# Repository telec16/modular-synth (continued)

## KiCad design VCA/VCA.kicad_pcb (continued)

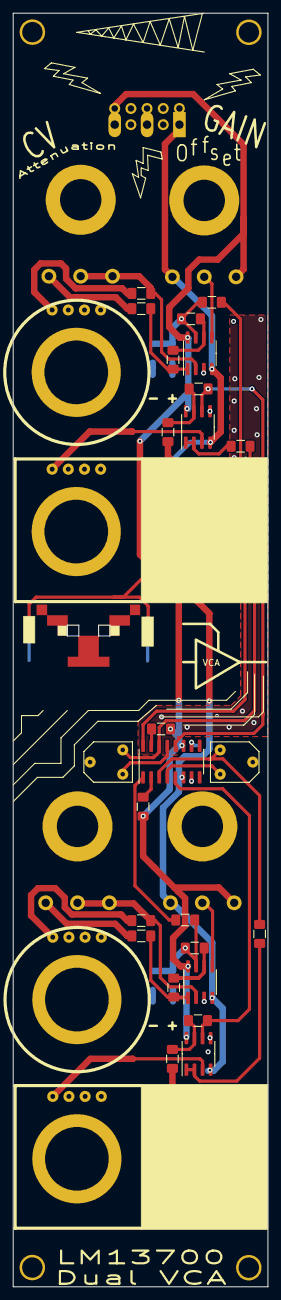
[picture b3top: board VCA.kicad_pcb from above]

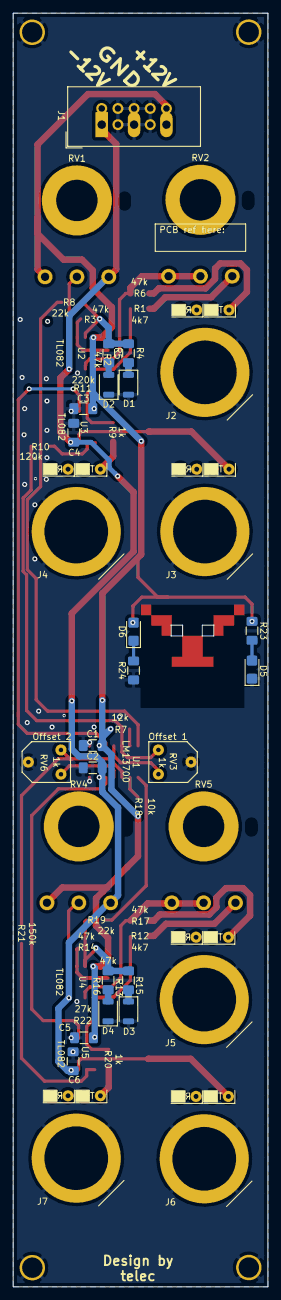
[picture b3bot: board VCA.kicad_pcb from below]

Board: 2 copper layers, 40.0 x 200.0 mm, 57 parts (19 on the bottom side), 41 nets.

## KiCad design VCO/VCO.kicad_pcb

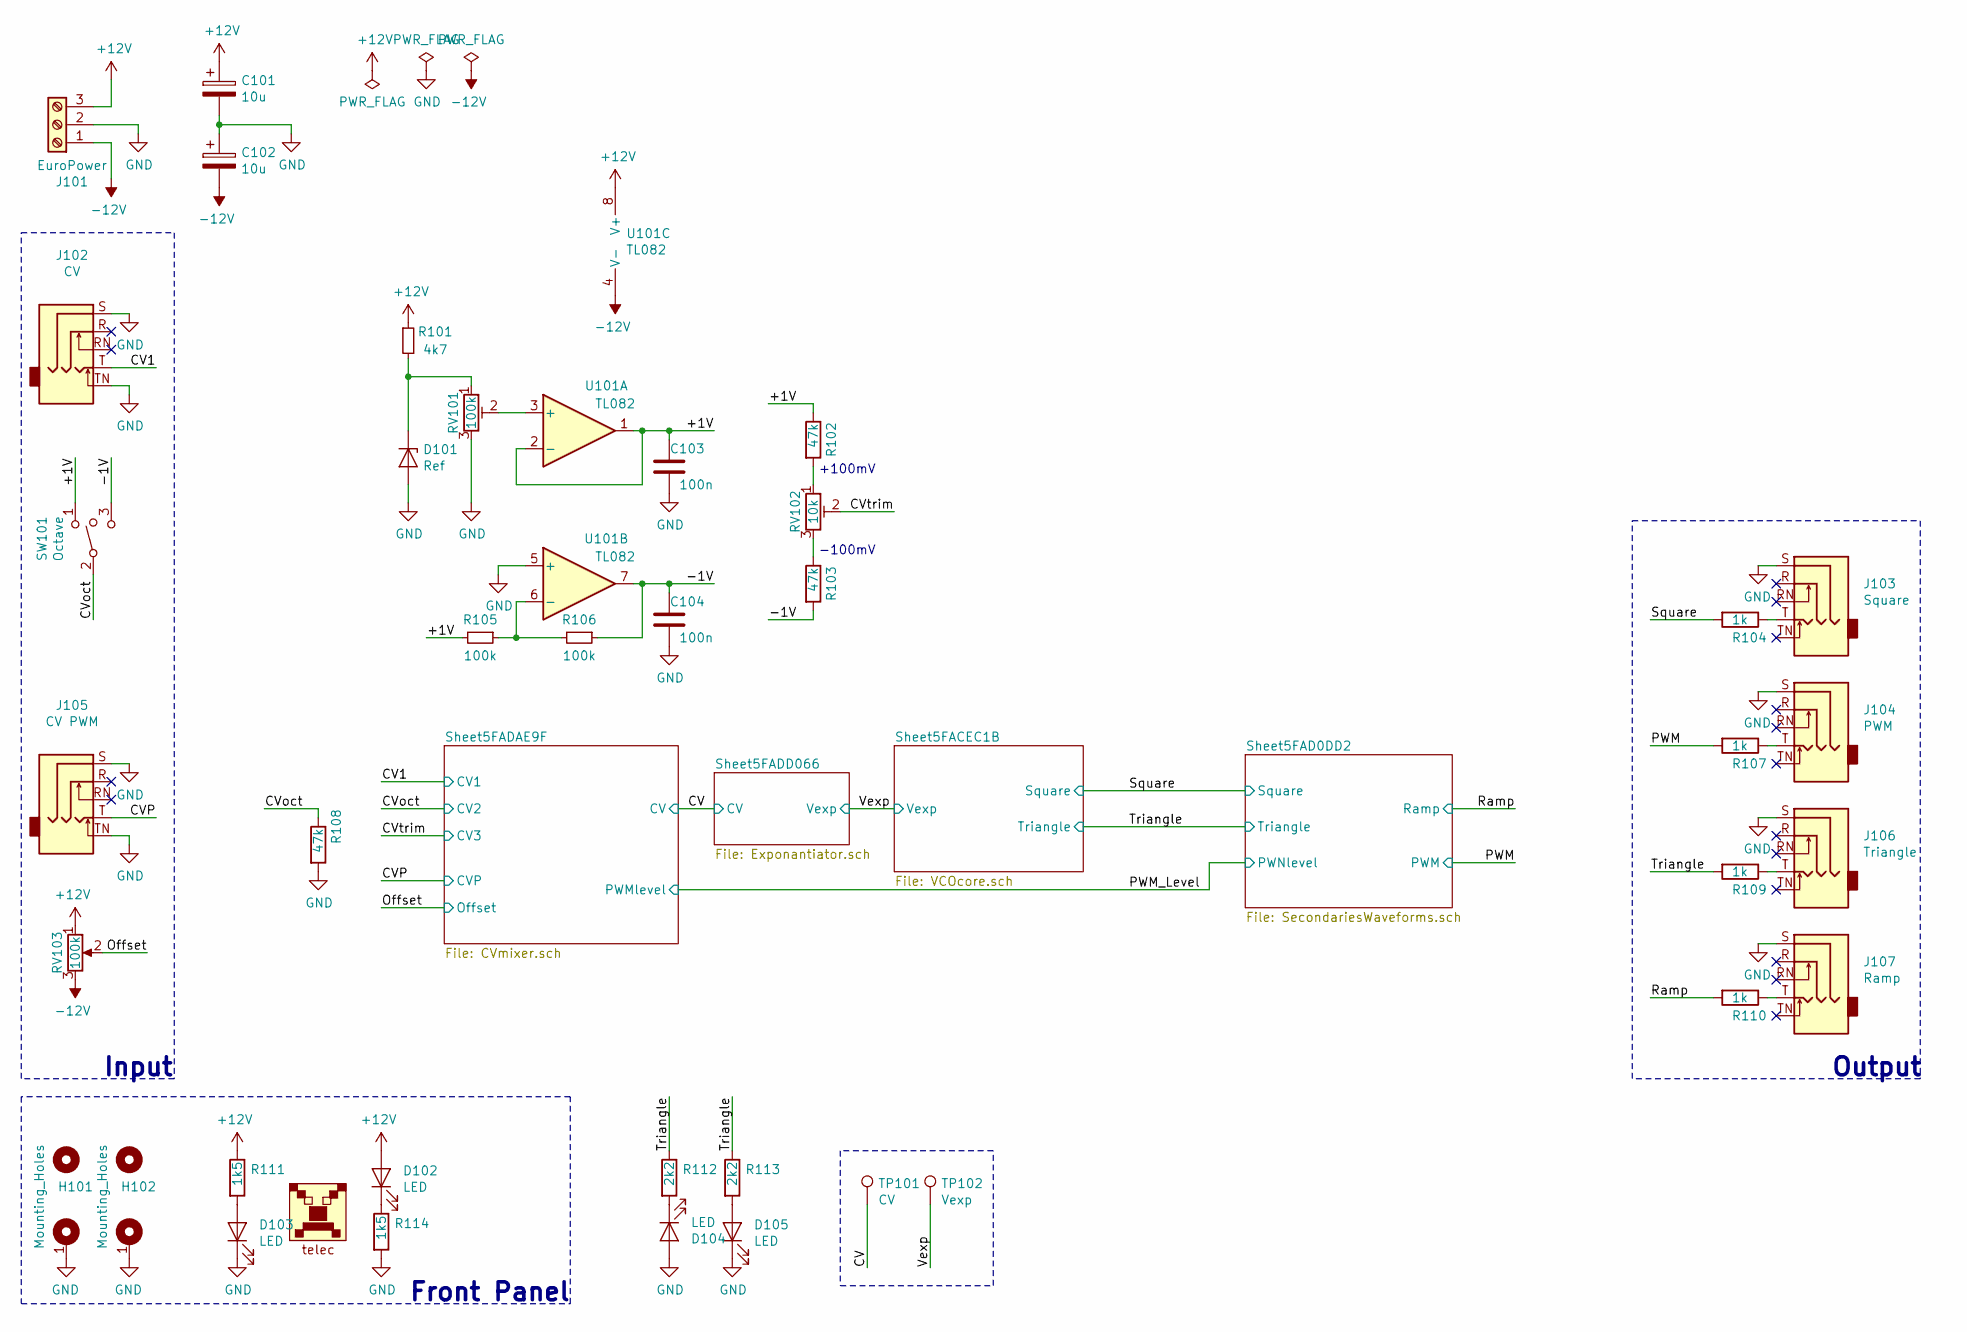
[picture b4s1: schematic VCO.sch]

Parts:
C101, C102: 10u; CP_Radial_D6.3mm_P2.50mm
C103, C104: 100n; C_0805_2012Metric_Pad1.15x1.40mm_HandSolder
D101: Ref; D_1206_3216Metric_Pad1.42x1.75mm_HandSolder
D102, D103: LED; LED_1206_3216Metric_Castellated
D104, D105: LED; LED_1206_3216Metric_ReverseMount_Hole1.8x2.4mm
H101, H102: Mounting_Holes; Kosmo_Panel_Dual_Mounting_Holes
J101: EuroPower
J102: CV; Jack_Hole_Square
J103: Square; Jack_Hole_Square
J104: PWM; Jack_Hole_Square
J105: CV PWM; Jack_Hole_Square
J106: Triangle; Jack_Hole_Square
J107: Ramp; Jack_Hole_Square
LOGO101: telec; telec-16
R101: 4k7; R_1206_3216Metric_Pad1.42x1.75mm_HandSolder
R102, R103, R108: 47k; R_Axial_DIN0204_L3.6mm_D1.6mm_P7.62mm_Horizontal
R104, R107, R109, R110: 1k; R_1206_3216Metric_Pad1.42x1.75mm_HandSolder
R105, R106: 100k; R_1206_3216Metric_Pad1.42x1.75mm_HandSolder
R111, R114: 1k5; R_1206_3216Metric_Pad1.42x1.75mm_HandSolder
R112, R113: 2k2; R_1206_3216Metric_Pad1.42x1.75mm_HandSolder
RV101: 100k; Potentiometer_Bourns_3296W_Vertical
RV102: 10k; Potentiometer_Bourns_3296W_Vertical
RV103: 100k; Potentiometer_Single_Vertical_Hole
SW101: Octave; Switch_Hole
TP101: CV; PinHeader_1x01_P2.54mm_Vertical
TP102: Vexp; PinHeader_1x01_P2.54mm_Vertical
U101: TL082; SOIC-8_3.9x4.9mm_P1.27mm

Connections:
+12V: C101.1, D102.2 (A), J101.3, R101.1, R111.1, RV103.1, U101.8 (V+); also elsewhere on the board
-12V: C102.2, J101.1, RV103.3, U101.4 (V-); also elsewhere on the board
/+1V: C103.1, R102.1, R105.2, SW101.1, U101.1, U101.2 (-)
/-1V: C104.1, R103.2, R106.1, SW101.3, U101.7
/CV: TP101.1; also elsewhere on the board
/CV1: J102.T; also elsewhere on the board
/CVP: J105.T; also elsewhere on the board
/CVoct: R108.1, SW101.2; also elsewhere on the board
/CVtrim: RV102.2; also elsewhere on the board
/Offset: RV103.2; also elsewhere on the board
/PWM: R107.2; also elsewhere on the board
/Ramp: R110.2; also elsewhere on the board
/Square: R104.2; also elsewhere on the board
/Triangle: R109.2, R112.1, R113.1; also elsewhere on the board
/Vexp: TP102.1; also elsewhere on the board
GND: C101.2, C102.1, C103.2, C104.2, D101.2 (A), D103.1 (K), D104.2 (A), D105.1 (K), H101.1, H102.1, J101.2, J102.S, J102.TN, J103.S, J104.S, J105.S, J105.TN, J106.S, J107.S, R108.2, R114.2, RV101.3, U101.5 (+); also elsewhere on the board
unnamed: D101.1 (K), R101.2, RV101.1
unnamed: D102.1 (K), R114.1
unnamed: D103.2 (A), R111.2
unnamed: D104.1 (K), R112.2
unnamed: D105.2 (A), R113.2
unnamed: J103.T, R104.1
unnamed: J104.T, R107.1
unnamed: J106.T, R109.1
unnamed: J107.T, R110.1
unnamed: R102.2, RV102.1
unnamed: R103.1, RV102.3
unnamed: R105.1, R106.2, U101.6 (-)
unnamed: RV101.2, U101.3 (+)

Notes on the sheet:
Output
Input
Front Panel
+100mV
-100mV

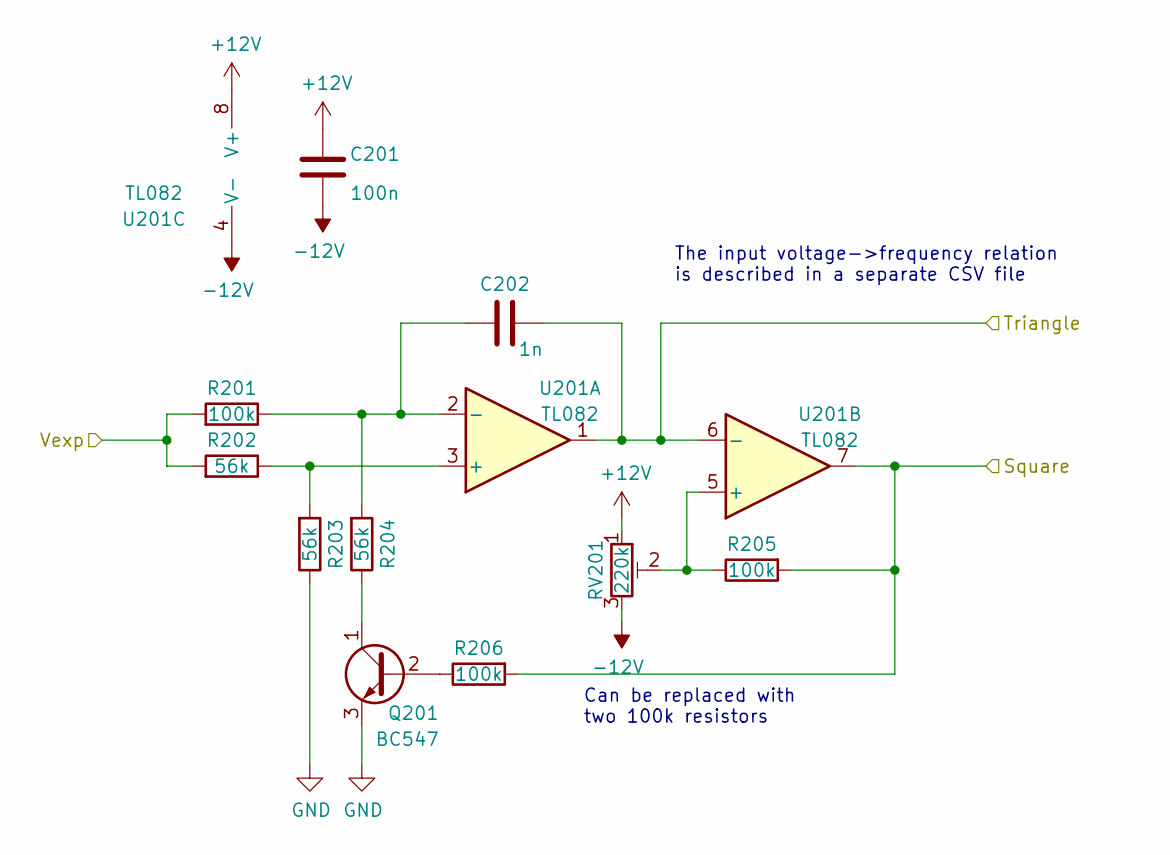
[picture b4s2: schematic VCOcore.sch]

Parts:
C201: 100n; C_0805_2012Metric_Pad1.15x1.40mm_HandSolder
C202: 1n; C_Disc_D7.0mm_W2.5mm_P5.00mm
Q201: BC547; TO-92_Inline_Wide
R201, R205, R206: 100k; R_Axial_DIN0204_L3.6mm_D1.6mm_P7.62mm_Horizontal
R202, R203, R204: 56k; R_Axial_DIN0204_L3.6mm_D1.6mm_P7.62mm_Horizontal
RV201: 220k; Potentiometer_P3.81mmx5.12mm_Vertical
U201: TL082; DIP-8_W7.62mm_LongPads

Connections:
+12V: C201.1, RV201.1, U201.8 (V+); also elsewhere on the board
-12V: C201.2, RV201.3, U201.4 (V-); also elsewhere on the board
/Square: R205.2, R206.2, U201.7; also elsewhere on the board
/Triangle: C202.1, U201.1, U201.6 (-); also elsewhere on the board
/Vexp: R201.2, R202.2; also elsewhere on the board
GND: Q201.3 (E), R203.1; also elsewhere on the board
unnamed: C202.2, R201.1, R204.2, U201.2 (-)
unnamed: Q201.1 (C), R204.1
unnamed: Q201.2 (B), R206.1
unnamed: R202.1, R203.2, U201.3 (+)
unnamed: R205.1, RV201.2, U201.5 (+)

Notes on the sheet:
Can be replaced with two 100k resistors
The input voltage->frequency relation is described in a separate CSV file

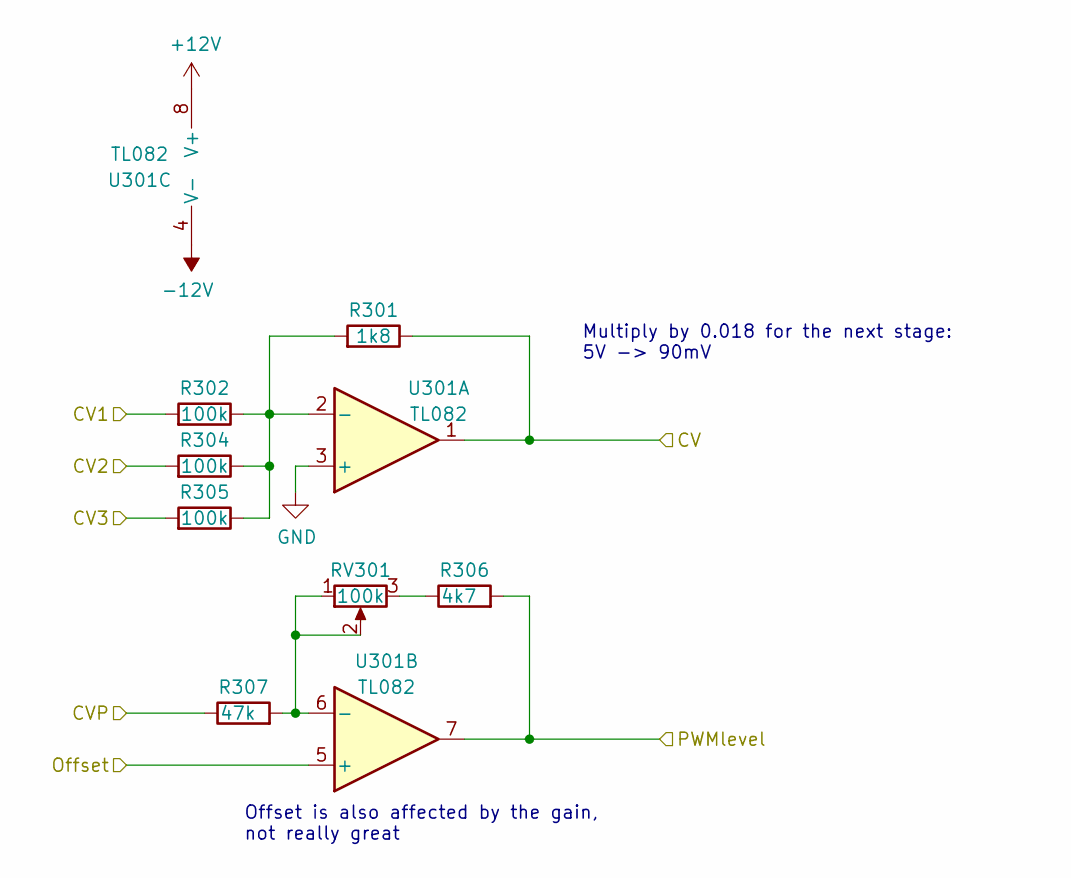
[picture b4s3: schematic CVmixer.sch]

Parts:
R301: 1k8; R_Axial_DIN0204_L3.6mm_D1.6mm_P7.62mm_Horizontal
R302, R304, R305: 100k; R_Axial_DIN0204_L3.6mm_D1.6mm_P7.62mm_Horizontal
R306: 4k7; R_Axial_DIN0204_L3.6mm_D1.6mm_P7.62mm_Horizontal
R307: 47k; R_Axial_DIN0204_L3.6mm_D1.6mm_P7.62mm_Horizontal
RV301: 100k; Potentiometer_Single_Vertical_Hole
U301: TL082; DIP-8_W7.62mm_LongPads

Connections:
+12V: U301.8 (V+); also elsewhere on the board
-12V: U301.4 (V-); also elsewhere on the board
/CV: R301.1, U301.1; also elsewhere on the board
/CV1: R302.2; also elsewhere on the board
/CVP: R307.1; also elsewhere on the board
/CVoct: R304.2; also elsewhere on the board
/CVtrim: R305.2; also elsewhere on the board
/Offset: U301.5 (+); also elsewhere on the board
/PWM_Level: R306.2, U301.7; also elsewhere on the board
GND: U301.3 (+); also elsewhere on the board
unnamed: R301.2, R302.1, R304.1, R305.1, U301.2 (-)
unnamed: R306.1, RV301.3
unnamed: R307.2, RV301.1, RV301.2, U301.6 (-)

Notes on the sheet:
Offset is also affected by the gain, not really great
Multiply by 0.018 for the next stage: 5V -> 90mV

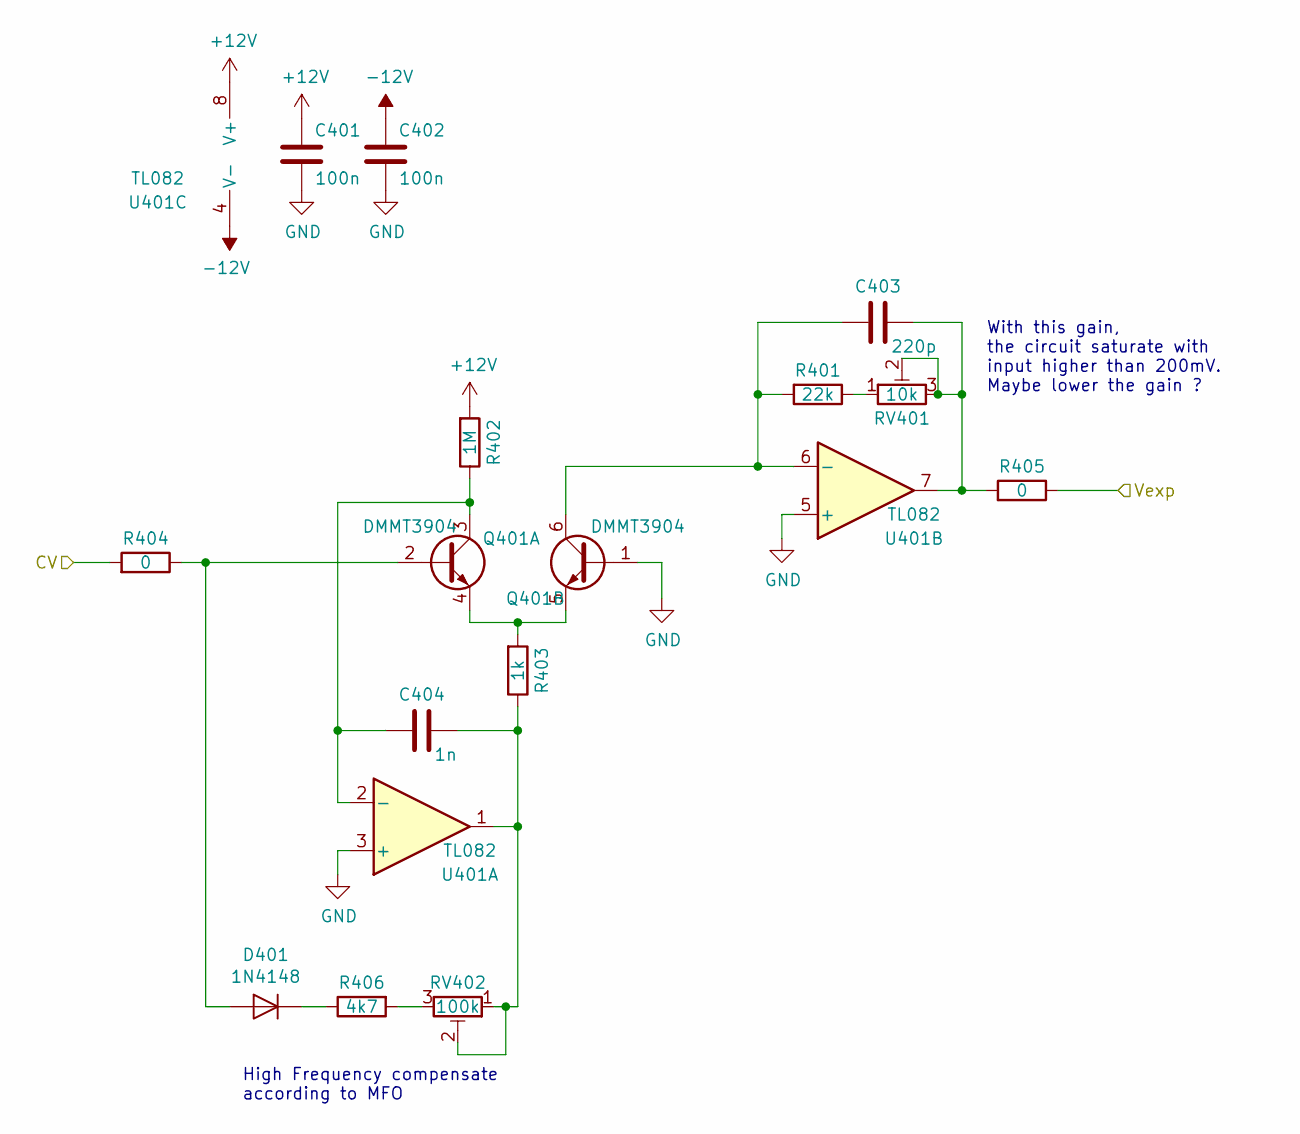
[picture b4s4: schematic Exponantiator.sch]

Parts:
C401, C402: 100n; C_0805_2012Metric_Pad1.15x1.40mm_HandSolder
C403: 220p; C_Disc_D7.0mm_W2.5mm_P5.00mm
C404: 1n; C_Disc_D7.0mm_W2.5mm_P5.00mm
D401: 1N4148; D_DO-35_SOD27_P7.62mm_Horizontal
Q401: DMMT3904; SOT-23-6_Handsoldering
R401: 22k; R_Axial_DIN0204_L3.6mm_D1.6mm_P7.62mm_Horizontal
R402: 1M; R_Axial_DIN0204_L3.6mm_D1.6mm_P7.62mm_Horizontal
R403: 1k; R_Axial_DIN0204_L3.6mm_D1.6mm_P7.62mm_Horizontal
R404, R405: 0; R_Axial_DIN0204_L3.6mm_D1.6mm_P7.62mm_Horizontal
R406: 4k7; R_Axial_DIN0204_L3.6mm_D1.6mm_P7.62mm_Horizontal
RV401: 10k; Potentiometer_Bourns_3296W_Vertical
RV402: 100k; Potentiometer_Bourns_3296W_Vertical
U401: TL082; DIP-8_W7.62mm_LongPads

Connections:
+12V: C401.1, R402.2, U401.8 (V+); also elsewhere on the board
-12V: C402.1, U401.4 (V-); also elsewhere on the board
/CV: R404.2; also elsewhere on the board
/Vexp: R405.1; also elsewhere on the board
GND: C401.2, C402.2, Q401.1 (B2), U401.3 (+), U401.5 (+); also elsewhere on the board
unnamed: C403.1, R405.2, RV401.2, RV401.3, U401.7
unnamed: C403.2, Q401.6 (C2), R401.2, U401.6 (-)
unnamed: C404.1, R403.1, RV402.1, RV402.2, U401.1
unnamed: C404.2, Q401.3 (C2), R402.1, U401.2 (-)
unnamed: D401.1 (K), R406.1
unnamed: D401.2 (A), Q401.2 (B2), R404.1
unnamed: Q401.4 (E2), Q401.5 (E2), R403.2
unnamed: R401.1, RV401.1
unnamed: R406.2, RV402.3

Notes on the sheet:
With this gain, the circuit saturate with input higher than 200mV. Maybe lower the gain ?
High Frequency compensate according to MFO

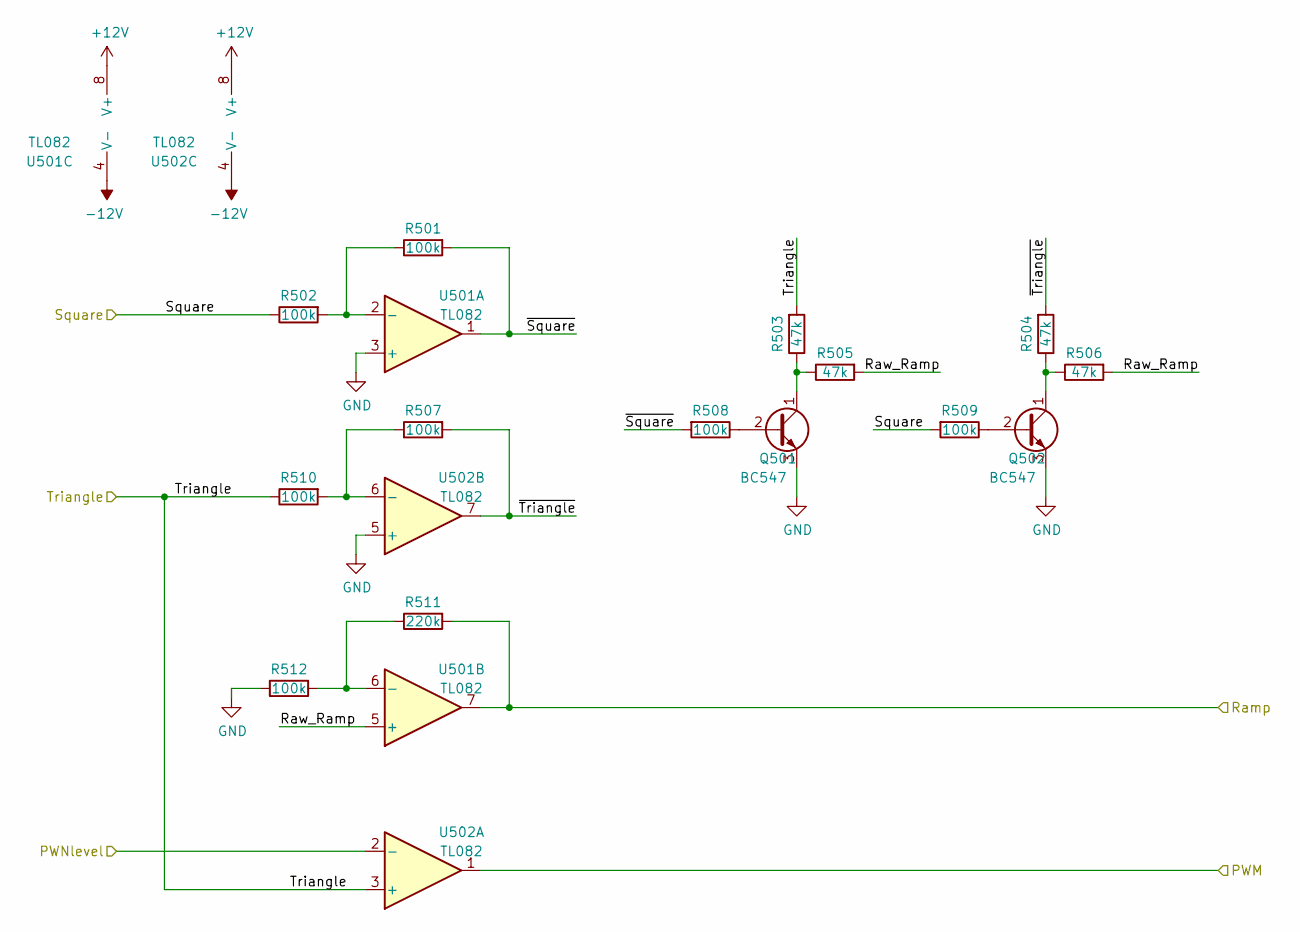
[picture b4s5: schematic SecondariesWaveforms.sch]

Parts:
Q501, Q502: BC547; TO-92_Inline_Wide
R501: 100k; R_Axial_DIN0204_L3.6mm_D1.6mm_P2.54mm_Vertical
R502, R507, R508, R509, R510, R512: 100k; R_Axial_DIN0204_L3.6mm_D1.6mm_P7.62mm_Horizontal
R503, R504, R505, R506: 47k; R_Axial_DIN0204_L3.6mm_D1.6mm_P7.62mm_Horizontal
R511: 220k; R_Axial_DIN0204_L3.6mm_D1.6mm_P7.62mm_Horizontal
U501, U502: TL082; DIP-8_W7.62mm_LongPads

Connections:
+12V: U501.8 (V+), U502.8 (V+); also elsewhere on the board
-12V: U501.4 (V-), U502.4 (V-); also elsewhere on the board
/PWM: U502.1; also elsewhere on the board
/PWM_Level: U502.2 (-); also elsewhere on the board
/Ramp: R511.2, U501.7; also elsewhere on the board
/Sheet5FAD0DD2/Raw_Ramp: R505.2, R506.2, U501.5 (+)
/Sheet5FAD0DD2/~Square: R501.2, R508.2, U501.1
/Sheet5FAD0DD2/~Triangle: R504.2, R507.2, U502.7
/Square: R502.1, R509.2; also elsewhere on the board
/Triangle: R503.2, R510.1, U502.3 (+); also elsewhere on the board
GND: Q501.3 (E), Q502.3 (E), R512.1, U501.3 (+), U502.5 (+); also elsewhere on the board
unnamed: Q501.1 (C), R503.1, R505.1
unnamed: Q501.2 (B), R508.1
unnamed: Q502.1 (C), R504.1, R506.1
unnamed: Q502.2 (B), R509.1
unnamed: R501.1, R502.2, U501.2 (-)
unnamed: R507.1, R510.2, U502.6 (-)
unnamed: R511.1, R512.2, U501.6 (-)

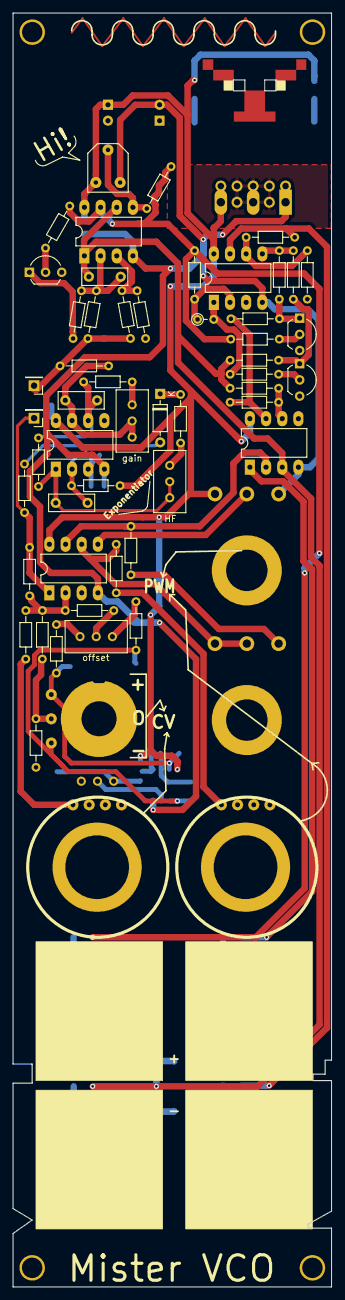
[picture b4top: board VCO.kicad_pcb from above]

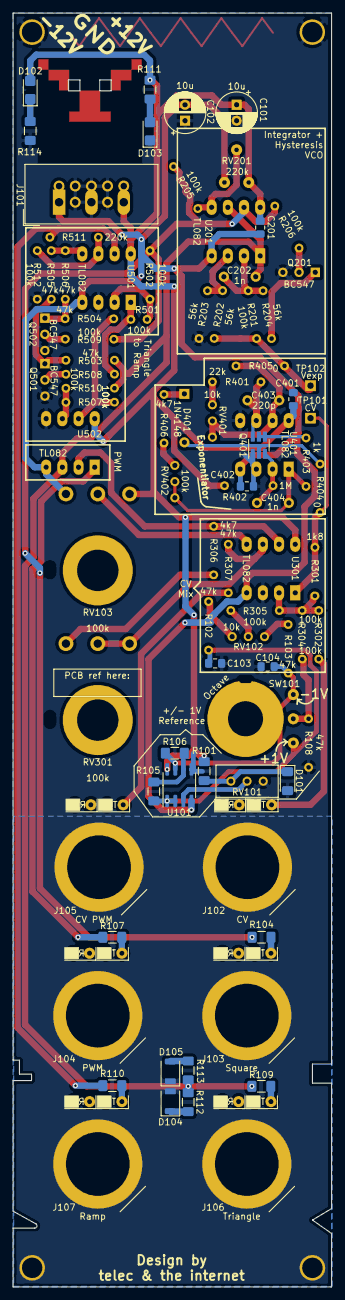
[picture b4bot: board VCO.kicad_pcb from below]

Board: 2 copper layers, 49.9 x 200.0 mm, 90 parts (27 on the bottom side), 57 nets.

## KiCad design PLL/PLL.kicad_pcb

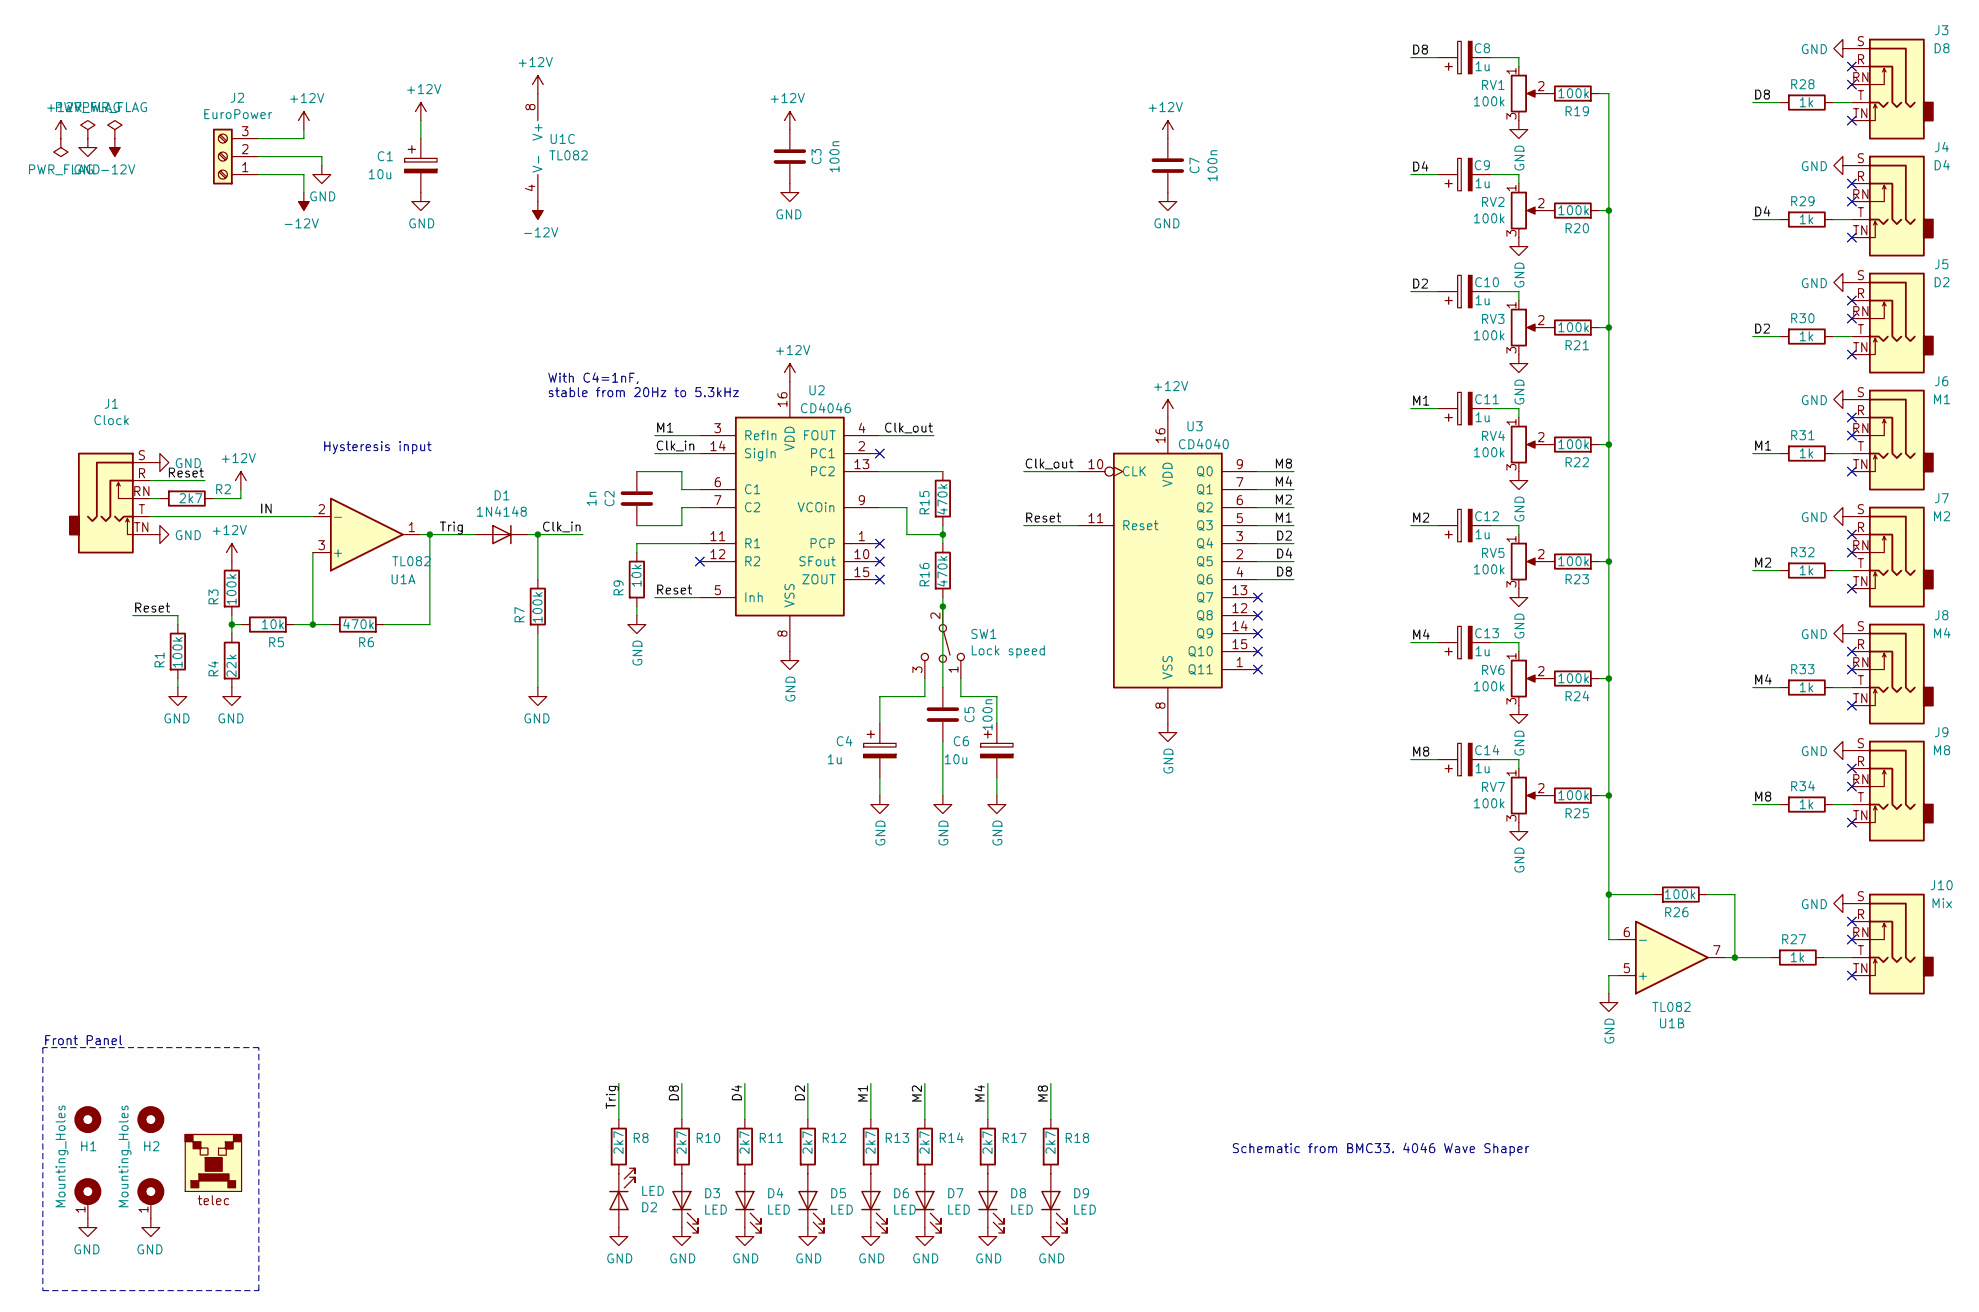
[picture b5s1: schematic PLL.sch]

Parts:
C1, C6: 10u; CP_Radial_D4.0mm_P1.50mm
C2: 1n; C_Disc_D7.0mm_W2.5mm_P5.00mm
C3, C5, C7: 100n; C_Disc_D7.0mm_W2.5mm_P5.00mm
C4, C8, C9, C10, C11, C12, C13, C14: 1u; CP_Radial_D4.0mm_P1.50mm
D1: 1N4148; D_1206_3216Metric_Pad1.42x1.75mm_HandSolder
D2, D3, D4, D5, D6, D7, D8, D9: LED; LED_1206_3216Metric_ReverseMount_Hole1.8x2.4mm
H1, H2: Mounting_Holes; Kosmo_Panel_Dual_Mounting_Holes
J1: Clock; Jack_Hole_Square
J2: EuroPower
J3: D8; Jack_Hole_Square
J4: D4; Jack_Hole_Square
J5: D2; Jack_Hole_Square
J6: M1; Jack_Hole_Square
J7: M2; Jack_Hole_Square
J8: M4; Jack_Hole_Square
J9: M8; Jack_Hole_Square
J10: Mix; Jack_Hole_Square
LOGO1: telec; telec-8
R1, R19, R20, R21, R22, R23, R24, R25: 100k; R_Axial_DIN0204_L3.6mm_D1.6mm_P7.62mm_Horizontal
R2: 2k7; R_Axial_DIN0204_L3.6mm_D1.6mm_P7.62mm_Horizontal
R3, R7, R26: 100k; R_1206_3216Metric_Pad1.42x1.75mm_HandSolder
R4: 22k; R_1206_3216Metric_Pad1.42x1.75mm_HandSolder
R5: 10k; R_1206_3216Metric_Pad1.42x1.75mm_HandSolder
R6: 470k; R_1206_3216Metric_Pad1.42x1.75mm_HandSolder
R8, R10, R11, R12, R13, R14, R17, R18: 2k7; R_1206_3216Metric_Pad1.42x1.75mm_HandSolder
R9: 10k; R_Axial_DIN0204_L3.6mm_D1.6mm_P7.62mm_Horizontal
R15, R16: 470k; R_Axial_DIN0204_L3.6mm_D1.6mm_P7.62mm_Horizontal
R27: 1k; R_1206_3216Metric_Pad1.42x1.75mm_HandSolder
R28, R29, R30, R31, R32, R33, R34: 1k; R_Axial_DIN0204_L3.6mm_D1.6mm_P7.62mm_Horizontal
RV1, RV2, RV3, RV4, RV5, RV6, RV7: 100k; Potentiometer_Single_Vertical_Hole
SW1: Lock speed; SW_L13.2mm_W7.9mm_P4.7mm
U1: TL082; SOIC-8_3.9x4.9mm_P1.27mm
U2: CD4046; DIP-16_W7.62mm_LongPads
U3: CD4040; DIP-16_W7.62mm_LongPads

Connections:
+12V: C1.1, C3.2, C7.2, J2.3, R2.1, R3.1, U1.8 (V+), U2.16 (VDD), U3.16 (VDD)
-12V: J2.1, U1.4 (V-)
/Clk_in: D1.1 (K), R7.1, U2.14 (SigIn)
/Clk_out: U2.4 (FOUT), U3.10 (CLK)
/D2: C10.1, R12.1, R30.2, U3.3 (Q4)
/D4: C9.1, R11.1, R29.2, U3.2 (Q5)
/D8: C8.1, R10.1, R28.2, U3.4 (Q6)
/IN: J1.T, U1.2 (-)
/M1: C11.1, R13.1, R31.2, U2.3 (RefIn), U3.5 (Q3)
/M2: C12.1, R14.1, R32.2, U3.6 (Q2)
/M4: C13.1, R17.1, R33.2, U3.7 (Q1)
/M8: C14.1, R18.1, R34.2, U3.9 (Q0)
/Reset: J1.R, R1.1, U2.5 (Inh), U3.11 (Reset)
/Trig: D1.2 (A), R6.2, R8.1, U1.1
GND: C1.2, C3.1, C4.2, C5.1, C6.2, C7.1, D2.2 (A), D3.1 (K), D4.1 (K), D5.1 (K), D6.1 (K), D7.1 (K), D8.1 (K), D9.1 (K), H1.1, H2.1, J1.S, J1.TN, J2.2, J3.S, J4.S, J5.S, J6.S, J7.S, J8.S, J9.S, J10.S, R1.2, R4.2, R7.2, R9.2, RV1.3, RV2.3, RV3.3, RV4.3, RV5.3, RV6.3, RV7.3, U1.5 (+), U2.8 (VSS), U3.8 (VSS)
unnamed: C2.1, U2.7 (C2)
unnamed: C2.2, U2.6 (C1)
unnamed: C4.1, SW1.3
unnamed: C5.2, R16.2, SW1.2
unnamed: C6.1, SW1.1
unnamed: C8.2, RV1.1
unnamed: C9.2, RV2.1
unnamed: C10.2, RV3.1
unnamed: C11.2, RV4.1
unnamed: C12.2, RV5.1
unnamed: C13.2, RV6.1
unnamed: C14.2, RV7.1
unnamed: D2.1 (K), R8.2
unnamed: D3.2 (A), R10.2
unnamed: D4.2 (A), R11.2
unnamed: D5.2 (A), R12.2
unnamed: D6.2 (A), R13.2
unnamed: D7.2 (A), R14.2
unnamed: D8.2 (A), R17.2
unnamed: D9.2 (A), R18.2
unnamed: J1.RN, R2.2
unnamed: J3.T, R28.1
unnamed: J4.T, R29.1
unnamed: J5.T, R30.1
unnamed: J6.T, R31.1
unnamed: J7.T, R32.1
unnamed: J8.T, R33.1
unnamed: J9.T, R34.1
unnamed: J10.T, R27.1
unnamed: R3.2, R4.1, R5.1
unnamed: R5.2, R6.1, U1.3 (+)
unnamed: R9.1, U2.11 (R1)
unnamed: R15.1, U2.13 (PC2)
unnamed: R15.2, R16.1, U2.9 (VCOin)
unnamed: R19.1, RV1.2
unnamed: R19.2, R20.2, R21.2, R22.2, R23.2, R24.2, R25.2, R26.2, U1.6 (-)
unnamed: R20.1, RV2.2
unnamed: R21.1, RV3.2
unnamed: R22.1, RV4.2
unnamed: R23.1, RV5.2
unnamed: R24.1, RV6.2
unnamed: R25.1, RV7.2
unnamed: R26.1, R27.2, U1.7

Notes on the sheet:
Front Panel
Schematic from BMC33. 4046 Wave Shaper
Hysteresis input
With C4=1nF, stable from 20Hz to 5.3kHz

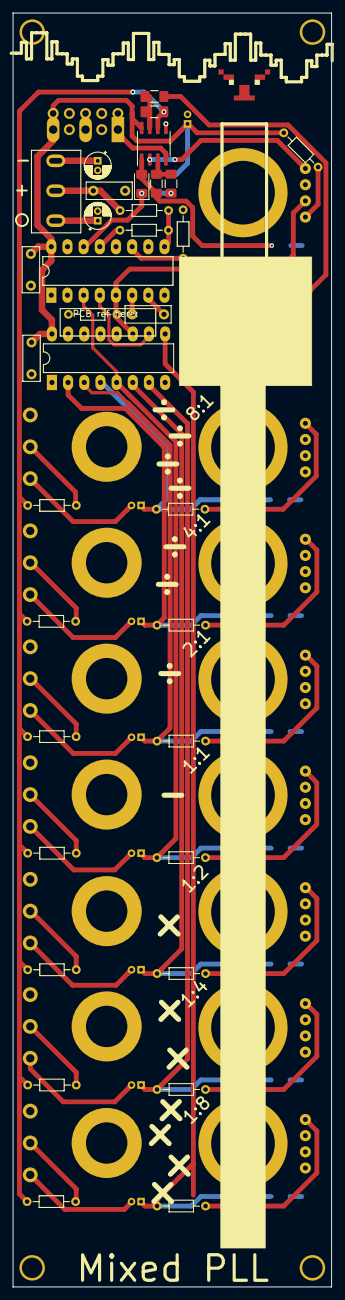
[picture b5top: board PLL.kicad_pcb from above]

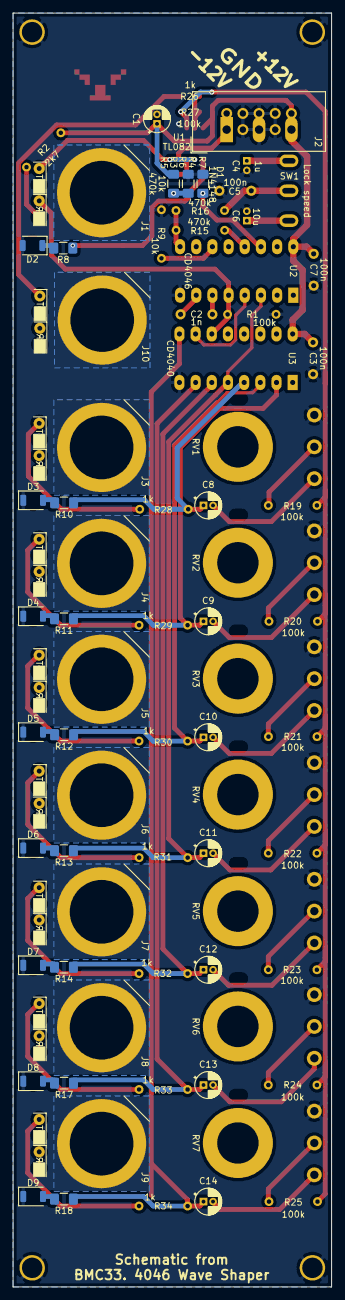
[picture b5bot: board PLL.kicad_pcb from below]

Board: 2 copper layers, 50.0 x 200.0 mm, 81 parts (28 on the bottom side), 58 nets.

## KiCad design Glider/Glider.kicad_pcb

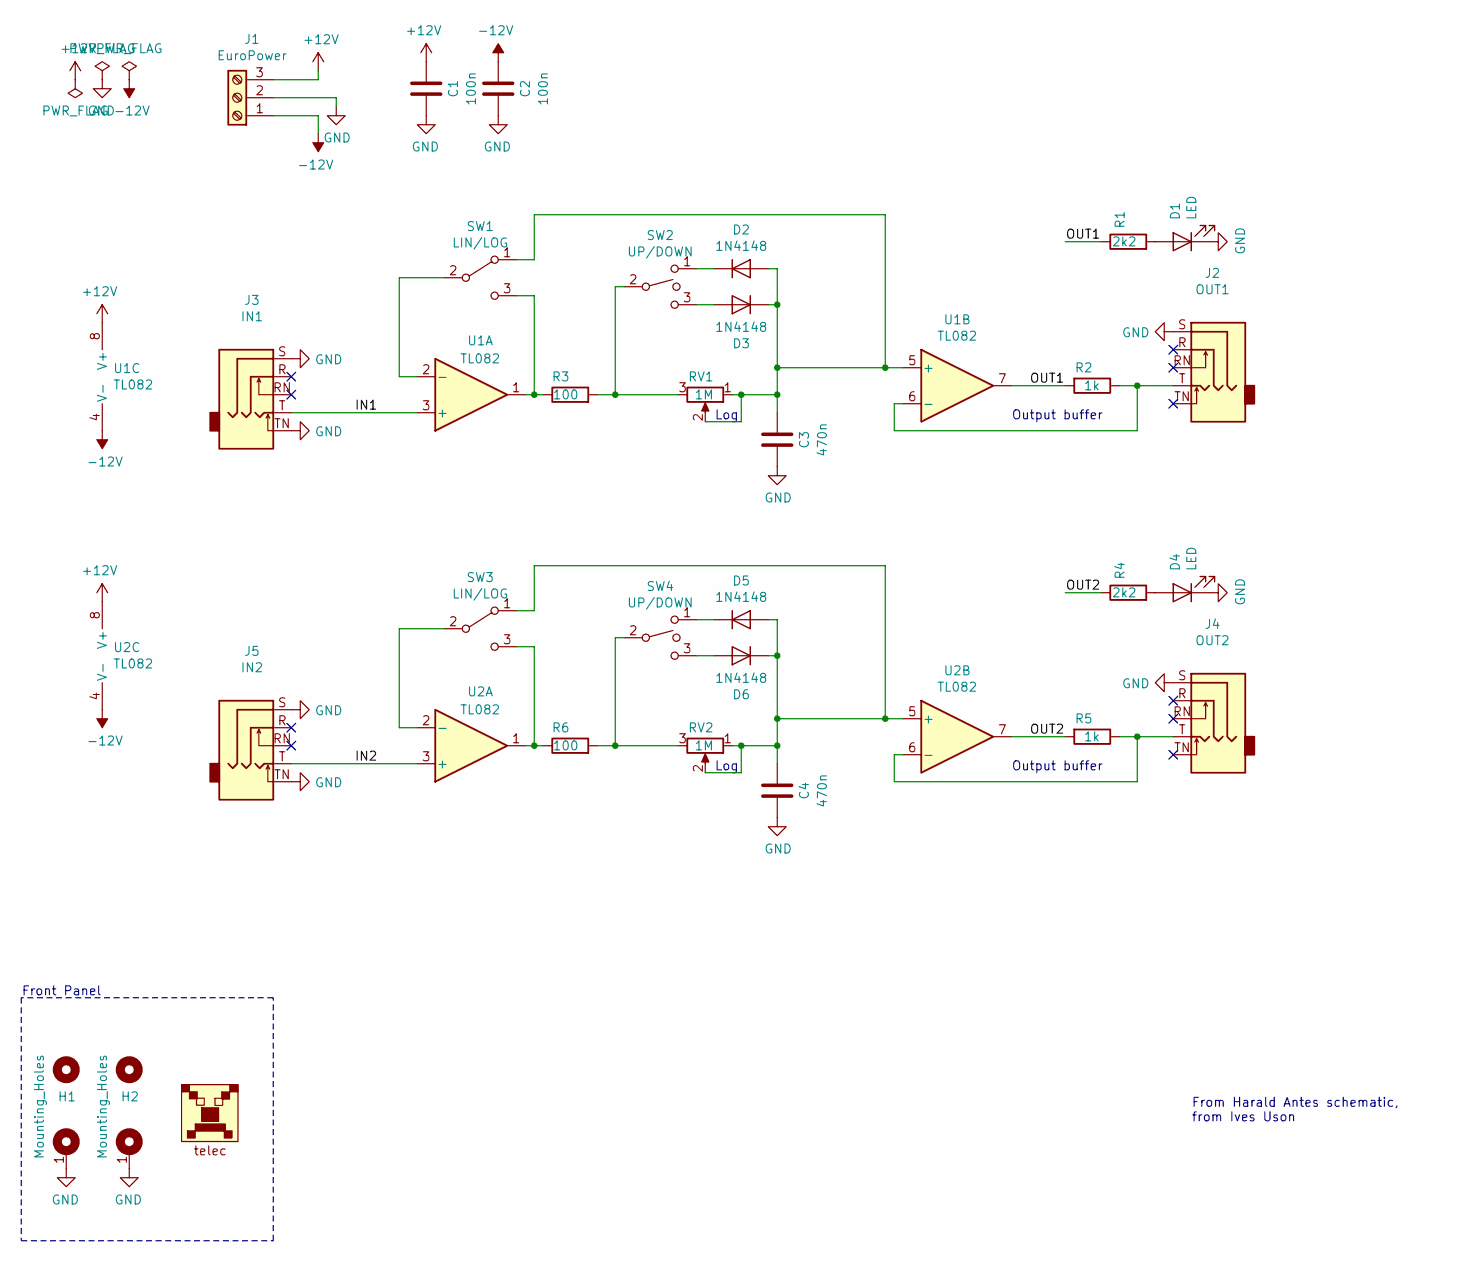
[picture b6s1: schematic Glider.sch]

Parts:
C1, C2: 100n; C_Disc_D7.0mm_W2.5mm_P5.00mm
C3, C4: 470n; C_Disc_D7.0mm_W2.5mm_P5.00mm
D1, D4: LED; LED_1206_3216Metric_ReverseMount_Hole1.8x2.4mm
D2, D3, D5, D6: 1N4148; D_DO-35_SOD27_P7.62mm_Horizontal
H1, H2: Mounting_Holes; Kosmo_Panel_Dual_Mounting_Holes
J1: EuroPower
J2: OUT1; Jack_Hole_Square
J3: IN1; Jack_Hole_Square
J4: OUT2; Jack_Hole_Square
J5: IN2; Jack_Hole_Square
LOGO1: telec; telec-8
R1, R4: 2k2; R_1206_3216Metric_Pad1.42x1.75mm_HandSolder
R2, R5: 1k; R_Axial_DIN0204_L3.6mm_D1.6mm_P7.62mm_Horizontal
R3, R6: 100; R_Axial_DIN0204_L3.6mm_D1.6mm_P7.62mm_Horizontal
RV1, RV2: 1M; Potentiometer_Alps_RK09K_Single_Vertical
SW1, SW3: LIN/LOG; SW_L13.2mm_W7.9mm_P4.7mm
SW2, SW4: UP/DOWN; SW_L13.2mm_W7.9mm_P4.7mm
U1, U2: TL082; DIP-8_W7.62mm_LongPads

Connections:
+12V: C1.2, J1.3, U1.8 (V+), U2.8 (V+)
-12V: C2.2, J1.1, U1.4 (V-), U2.4 (V-)
/IN1: J3.T, U1.3 (+)
/IN2: J5.T, U2.3 (+)
/OUT1: R1.1, R2.2, U1.7
/OUT2: R4.1, R5.2, U2.7
GND: C1.1, C2.1, C3.1, C4.1, D1.1 (K), D4.1 (K), H1.1, H2.1, J1.2, J2.S, J3.S, J3.TN, J4.S, J5.S, J5.TN
unnamed: C3.2, D2.2 (A), D3.1 (K), RV1.1, RV1.2, SW1.1 (A), U1.5 (+)
unnamed: C4.2, D5.2 (A), D6.1 (K), RV2.1, RV2.2, SW3.1 (A), U2.5 (+)
unnamed: D1.2 (A), R1.2
unnamed: D2.1 (K), SW2.1
unnamed: D3.2 (A), SW2.3
unnamed: D4.2 (A), R4.2
unnamed: D5.1 (K), SW4.1
unnamed: D6.2 (A), SW4.3
unnamed: J2.T, R2.1, U1.6 (-)
unnamed: J4.T, R5.1, U2.6 (-)
unnamed: R3.1, SW1.3 (C), U1.1
unnamed: R3.2, RV1.3, SW2.2
unnamed: R6.1, SW3.3 (C), U2.1
unnamed: R6.2, RV2.3, SW4.2
unnamed: SW1.2 (B), U1.2 (-)
unnamed: SW3.2 (B), U2.2 (-)

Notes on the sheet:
Output buffer
Front Panel
Log
From Harald Antes schematic, from Ives Uson

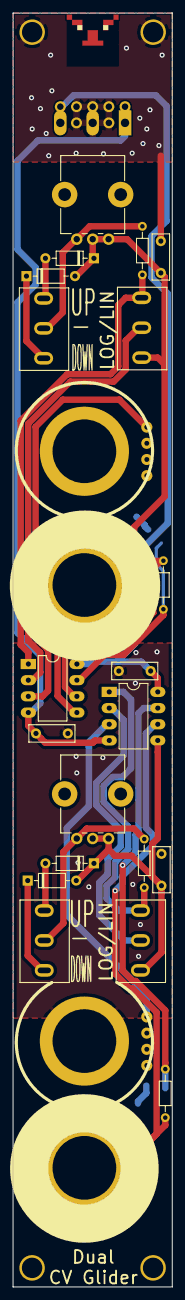
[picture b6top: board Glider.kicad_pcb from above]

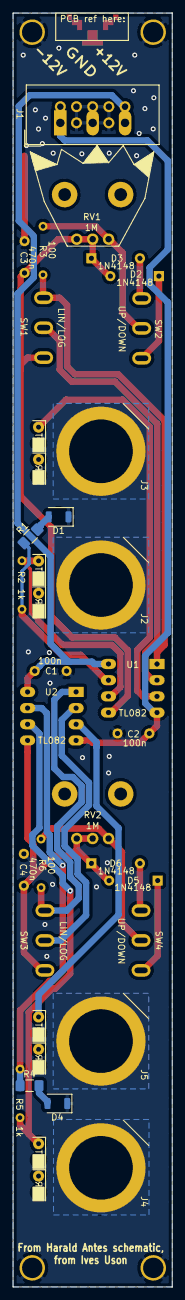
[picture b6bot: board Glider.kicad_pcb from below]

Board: 2 copper layers, 25.0 x 200.0 mm, 32 parts (5 on the bottom side), 23 nets.
